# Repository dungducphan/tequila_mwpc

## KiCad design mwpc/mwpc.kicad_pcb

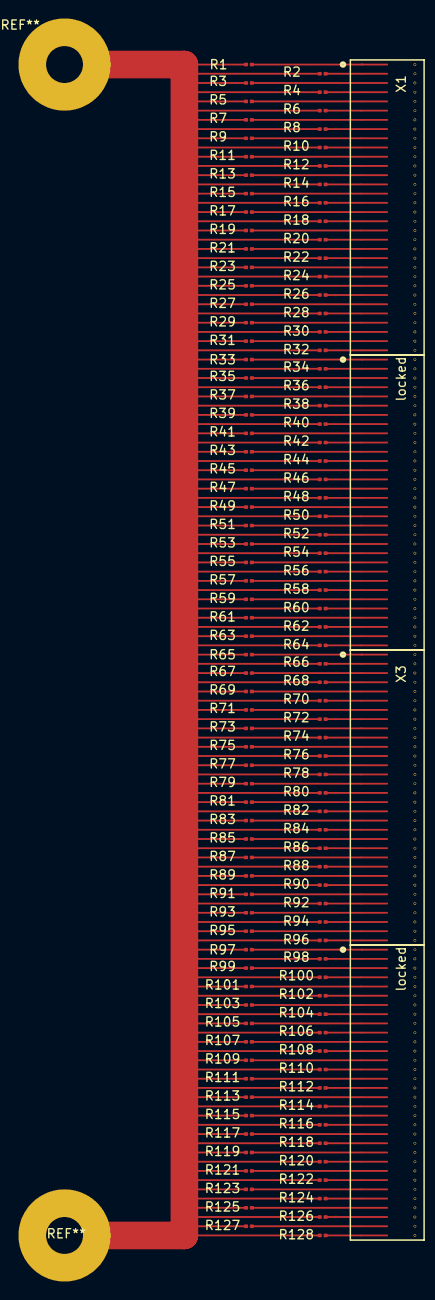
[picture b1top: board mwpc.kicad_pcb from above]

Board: 2 copper layers, 132 parts (0 on the bottom side), 33 nets, no tracks yet.

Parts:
R1, R2, R3, R4, R5, R6, R7, R8, R9, R10, R11, R12, R13, R14, R15, R16, R17, R18, R19, R20, R21, R22, R23, R24, R25, R26, R27, R28, R29, R30, R31, R32, R33, R34, R35, R36, R37, R38, R39, R40, R41, R42, R43, R44, R45, R46, R47, R48, R49, R50, R51, R52, R53, R54, R55, R56, R57, R58, R59, R60, R61, R62, R63, R64, R65, R66, R67, R68, R69, R70, R71, R72, R73, R74, R75, R76, R77, R78, R79, R80, R81, R82, R83, R84, R85, R86, R87, R88, R89, R90, R91, R92, R93, R94, R95, R96, R97, R98, R99, R100, R101, R102, R103, R104, R105, R106, R107, R108, R109, R110, R111, R112, R113, R114, R115, R116, R117, R118, R119, R120, R121, R122, R123, R124, R125, R126, R127, R128: 100k; R_0201_0603Metric
X1, X3: MWPC_HVT; MWPC_HVT_SMD
locked: MWPC_HVT; MWPC_HVT_SMD
locked#2: MWPC_HVT; MWPC_HVT_SMD

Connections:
unnamed: R1.2, R33.2, R65.2, R97.2, X1.1 (W), X3.1 (W), locked.1 (W), locked#2.1 (W)
unnamed: R2.2, R34.2, R66.2, R98.2, X1.2 (W), X3.2 (W), locked.2 (W), locked#2.2 (W)
unnamed: R3.2, R35.2, R67.2, R99.2, X1.3 (W), X3.3 (W), locked.3 (W), locked#2.3 (W)
unnamed: R4.2, R36.2, R68.2, R100.2, X1.4 (W), X3.4 (W), locked.4 (W), locked#2.4 (W)
unnamed: R5.2, R37.2, R69.2, R101.2, X1.5 (W), X3.5 (W), locked.5 (W), locked#2.5 (W)
unnamed: R6.2, R38.2, R70.2, R102.2, X1.6 (W), X3.6 (W), locked.6 (W), locked#2.6 (W)
unnamed: R7.2, R39.2, R71.2, R103.2, X1.7 (W), X3.7 (W), locked.7 (W), locked#2.7 (W)
unnamed: R8.2, R40.2, R72.2, R104.2, X1.8 (W), X3.8 (W), locked.8 (W), locked#2.8 (W)
unnamed: R9.2, R41.2, R73.2, R105.2, X1.9 (W), X3.9 (W), locked.9 (W), locked#2.9 (W)
unnamed: R10.2, R42.2, R74.2, R106.2, X1.10 (W), X3.10 (W), locked.10 (W), locked#2.10 (W)
unnamed: R11.2, R43.2, R75.2, R107.2, X1.11 (W), X3.11 (W), locked.11 (W), locked#2.11 (W)
unnamed: R12.2, R44.2, R76.2, R108.2, X1.12 (W), X3.12 (W), locked.12 (W), locked#2.12 (W)
unnamed: R13.2, R45.2, R77.2, R109.2, X1.13 (W), X3.13 (W), locked.13 (W), locked#2.13 (W)
unnamed: R14.2, R46.2, R78.2, R110.2, X1.14 (W), X3.14 (W), locked.14 (W), locked#2.14 (W)
unnamed: R15.2, R47.2, R79.2, R111.2, X1.15 (W), X3.15 (W), locked.15 (W), locked#2.15 (W)
unnamed: R16.2, R48.2, R80.2, R112.2, X1.16 (W), X3.16 (W), locked.16 (W), locked#2.16 (W)
unnamed: R17.2, R49.2, R81.2, R113.2, X1.17 (W), X3.17 (W), locked.17 (W), locked#2.17 (W)
unnamed: R18.2, R50.2, R82.2, R114.2, X1.18 (W), X3.18 (W), locked.18 (W), locked#2.18 (W)
unnamed: R19.2, R51.2, R83.2, R115.2, X1.19 (W), X3.19 (W), locked.19 (W), locked#2.19 (W)
unnamed: R20.2, R52.2, R84.2, R116.2, X1.20 (W), X3.20 (W), locked.20 (W), locked#2.20 (W)
unnamed: R21.2, R53.2, R85.2, R117.2, X1.21 (W), X3.21 (W), locked.21 (W), locked#2.21 (W)
unnamed: R22.2, R54.2, R86.2, R118.2, X1.22 (W), X3.22 (W), locked.22 (W), locked#2.22 (W)
unnamed: R23.2, R55.2, R87.2, R119.2, X1.23 (W), X3.23 (W), locked.23 (W), locked#2.23 (W)
unnamed: R24.2, R56.2, R88.2, R120.2, X1.24 (W), X3.24 (W), locked.24 (W), locked#2.24 (W)
unnamed: R25.2, R57.2, R89.2, R121.2, X1.25 (W), X3.25 (W), locked.25 (W), locked#2.25 (W)
unnamed: R26.2, R58.2, R90.2, R122.2, X1.26 (W), X3.26 (W), locked.26 (W), locked#2.26 (W)
unnamed: R27.2, R59.2, R91.2, R123.2, X1.27 (W), X3.27 (W), locked.27 (W), locked#2.27 (W)
unnamed: R28.2, R60.2, R92.2, R124.2, X1.28 (W), X3.28 (W), locked.28 (W), locked#2.28 (W)
unnamed: R29.2, R61.2, R93.2, R125.2, X1.29 (W), X3.29 (W), locked.29 (W), locked#2.29 (W)
unnamed: R30.2, R62.2, R94.2, R126.2, X1.30 (W), X3.30 (W), locked.30 (W), locked#2.30 (W)
unnamed: R31.2, R63.2, R95.2, R127.2, X1.31 (W), X3.31 (W), locked.31 (W), locked#2.31 (W)
unnamed: R32.2, R64.2, R96.2, R128.2, X1.32 (W), X3.32 (W), locked.32 (W), locked#2.32 (W)
VS: R1.1, R2.1, R3.1, R4.1, R5.1, R6.1, R7.1, R8.1, R9.1, R10.1, R11.1, R12.1, R13.1, R14.1, R15.1, R16.1, R17.1, R18.1, R19.1, R20.1, R21.1, R22.1, R23.1, R24.1, R25.1, R26.1, R27.1, R28.1, R29.1, R30.1, R31.1, R32.1, R33.1, R34.1, R35.1, R36.1, R37.1, R38.1, R39.1, R40.1, R41.1, R42.1, R43.1, R44.1, R45.1, R46.1, R47.1, R48.1, R49.1, R50.1, R51.1, R52.1, R53.1, R54.1, R55.1, R56.1, R57.1, R58.1, R59.1, R60.1, R61.1, R62.1, R63.1, R64.1, R65.1, R66.1, R67.1, R68.1, R69.1, R70.1, R71.1, R72.1, R73.1, R74.1, R75.1, R76.1, R77.1, R78.1, R79.1, R80.1, R81.1, R82.1, R83.1, R84.1, R85.1, R86.1, R87.1, R88.1, R89.1, R90.1, R91.1, R92.1, R93.1, R94.1, R95.1, R96.1, R97.1, R98.1, R99.1, R100.1, R101.1, R102.1, R103.1, R104.1, R105.1, R106.1, R107.1, R108.1, R109.1, R110.1, R111.1, R112.1, R113.1, R114.1, R115.1, R116.1, R117.1, R118.1, R119.1, R120.1, R121.1, R122.1, R123.1, R124.1, R125.1, R126.1, R127.1, R128.1

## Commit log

2022-06-23 KiCAD design for MWPC.
2022-06-24 Rearrange the components on the PCB.

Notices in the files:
mwpc/mwpc.kicad_pcb:
creativecommons.org/licenses/by/4.0
License: CC BY 4.0
